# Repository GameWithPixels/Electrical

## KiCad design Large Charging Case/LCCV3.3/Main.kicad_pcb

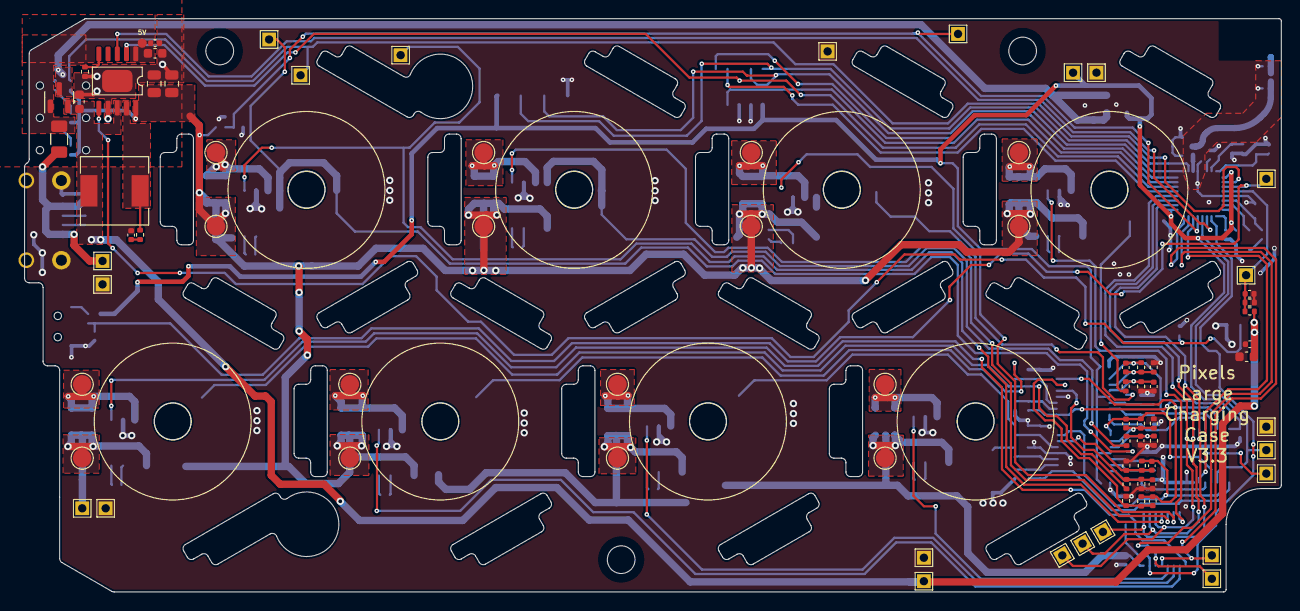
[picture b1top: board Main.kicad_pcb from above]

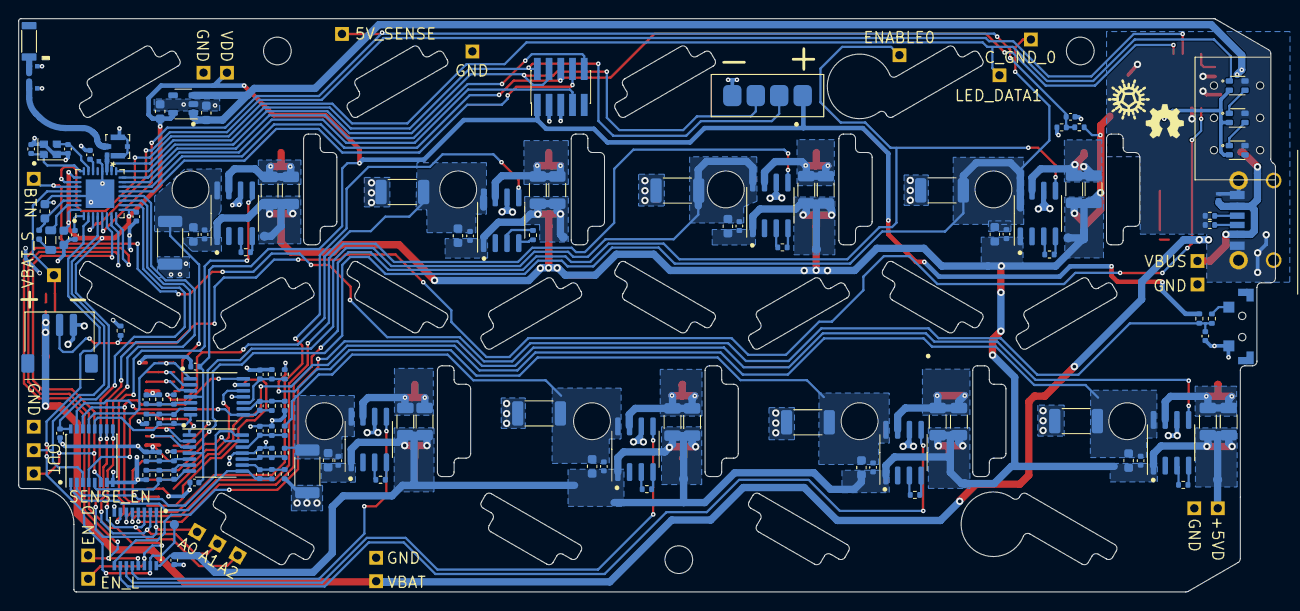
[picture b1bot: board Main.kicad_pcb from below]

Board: 2 copper layers, 136.2 x 62.1 mm, 225 parts (139 on the bottom side), 109 nets.

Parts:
AE1: Antenna_Chip; CHIP_ANT
C1, C2, C12, C16, C20, C24, C28, C32, C36, C44, C45, C52, C53, C56, C74: 10uF 10V 20%; C_0603_1608Metric
C3, C4, C10, C11, C15, C19, C23, C27, C31, C35, C39, C40, C41, C42, C43, C55, C75: 0.1uF 10V 20%; C_0402_1005Metric
C5, C6: 8pF 10V 10%; C_0402_1005Metric
C7: 100pF NP0 10V 5%; C_0402_1005Metric
C8, C9: 0.8pF 10V 5% NP0; 0402_RF
C13, C17, C21, C25, C29, C33, C37, C57: 100nF 50V NP0; C_1206_3216Metric
C14, C18, C22, C26, C30, C34, C38, C58: DNP; C_1206_3216Metric
C46: 3.3nF 50V 10%; C_0402_1005Metric
C47, C48: 22uF 10V 20%; C_0805_2012Metric
C49, C50, C59, C60, C61, C62, C63, C64, C65, C66, C67, C68, C69, C70, C71, C72: 1nF 10V 20%; C_0402_1005Metric
C51, C54: 10nF 25V 10%; C_0402_1005Metric
C73: DNP; 0402_RF
D1, D2, D3: TX1812Z_2020
D4: BAT54C; SOT-23
D5: D_TVS; DFN
F1: 1500mA <150mR; Fuse_1206_3216Metric
J1: Conn_02x05_Odd_Even; PinHeader_2x05_P1.27mm_Vertical_SMD
J2, J5, J8, J11, J14, J17, J20, J25: Coil B; TestPoint_Pad_D2.0mm
J3, J6, J9, J12, J15, J18, J21, J26: TX_Coil; TX Coil
J4, J7, J10, J13, J16, J19, J22, J27: Coil A; TestPoint_Pad_D2.0mm
J23: USB_C_Receptacle_USB2.0; USB-C-SMD_10P-P1.00-L6.8-W8.9
J24: Conn_01x03; Battery_Socket_1.5mm_3PIN
J28: DNP; MFH3.RECE.20369.001E.01
L1: 10uH 100mA 10%; L_0805_2012Metric
L2: 15nH; L_0402_1005Metric
L3: 1.5nH 5%; 0402_RF
L4: 2.2uH 1.5A 10%; SPM6530
L6: 3.9nH 5%; 0402_RF
P1: heard4; 4x2.54mm_SMD
R1: 10k 5%; R_0402_1005Metric
R2: 1k 1%; R_0402_1005Metric
R4, R7, R10, R13, R16, R33, R38, R74: 200K 1%; R_0402_1005Metric
R17: 82K 1%; R_0402_1005Metric
R18: 120k 1%; R_0402_1005Metric
R21, R25, R28, R32, R39, R43, R44, R48, R49, R53, R54, R58, R59, R63, R64, R68: 100k 0.1%; R_0402_1005Metric
R22, R24, R29, R31, R40, R42, R45, R47, R50, R52, R55, R57, R60, R62, R65, R67: 2k 0.1%; R_0402_1005Metric
R23, R30, R41, R46, R51, R56, R61, R66: 100mR 0.5W 1%; R_2010_5025Metric
R26, R27: 5.1k 1%; R_0402_1005Metric
R34, R71: 4.02M 1%; R_0402_1005Metric
R36, R72: 10M 1%; R_0402_1005Metric
R69: 1R 5%; R_0402_1005Metric
SW1: SW_Push; TSB002
U1: N52810_QFN32; QFN-32-1EP_5x5mm_P0.5mm_EP3.1x3.1mm
U3, U5, U7, U9, U11, U13, U15, U23: XKT520; SOIC-8_3.9x4.9mm_P1.27mm
U16: ETA9882; ESSOP10
U17: 74HC4051PW; SSOP-16_4.4x5.2mm_P0.65mm
U18, U20: LM2902; TSSOP-14_4.4x5mm_P0.65mm
U19: 74HCT259PW; SSOP-16_4.4x5.2mm_P0.65mm
U22: ME6215; SOT-23-5
W1: LED_DATA1; TestPoint_1.5x1.5_Drill0.9mm
W2, W3, W6, W7, W44, W45: GND; TestPoint_1.5x1.5_Drill0.9mm
W4, W9, W14, W19, W24, W29, W34, W71: R; TEST_PIN
W5: 5V_SENSE; TestPoint_1.5x1.5_Drill0.9mm
W11: VBAT; TestPoint_1.5x1.5_Drill0.9mm
W39: ENABLE0; TestPoint_1.5x1.5_Drill0.9mm
W40: C_GND_0; TestPoint_1.5x1.5_Drill0.9mm
W41: A2; TestPoint_1.5x1.5_Drill0.9mm
W42: A1; TestPoint_1.5x1.5_Drill0.9mm
W43: A0; TestPoint_1.5x1.5_Drill0.9mm
W47: OUT; TestPoint_1.5x1.5_Drill0.9mm
W48: SENSE_EN; TestPoint_1.5x1.5_Drill0.9mm
W57: EN_D; TestPoint_1.5x1.5_Drill0.9mm
W58: EN_L; TestPoint_1.5x1.5_Drill0.9mm
W59: CHARGER_CLR; TEST_PIN
W61: VBUS; TestPoint_1.5x1.5_Drill0.9mm
W62: 5V; TEST_PIN
W65: +5VD; TestPoint_1.5x1.5_Drill0.9mm
W68: VDD; TestPoint_1.5x1.5_Drill0.9mm
W70: VBAT_S; TestPoint_1.5x1.5_Drill0.9mm
W76: BTN; TestPoint_1.5x1.5_Drill0.9mm
Y1: 32MHz 40ppm; Crystal_SMD_2016-4Pin_2.0x1.6mm

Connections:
+5V: C43.1, C44.1, D4.1, F1.2, U16.1 (VIN), W62.1
+5VD: C11.1, C12.1, C13.2, C14.2, C15.1, C16.1, C17.2, C18.2, C19.1, C20.1, C21.2, C22.2, C23.1, C24.1, C25.2, C26.2, C27.1, C28.1, C29.2, C30.2, C31.1, C32.1, C33.2, C34.2, C35.1, C36.1, C37.2, C38.2, C42.1, C47.1, C48.1, C55.1, C56.1, C57.2, C58.2, D1.2 (VCC), D2.2 (VCC), D3.2 (VCC), J2.1, J5.1, J8.1, J11.1, J14.1, J17.1, J20.1, J25.1, R71.1, U3.1 (VDD), U5.1 (VDD), U7.1 (VDD), U9.1 (VDD), U11.1 (VDD), U13.1 (VDD), U15.1 (VDD), U16.10 (VOUT), U19.16 (VCC), U23.1 (VDD), W4.1, W9.1, W14.1, W19.1, W24.1, W29.1, W34.1, W65.1, W71.1
+BATT: C45.1, C74.1, C75.1, D4.2, J24.3, L4.2, R34.1, U16.8 (BAT), W11.1
/ANTENNA: AE1.1 (FEED), C73.1, L3.2
/ANT_50: C8.1, J28.4 (RF), L3.1, L6.2
/ANT_NRF: C9.1, L6.1, U1.19 (ANT)
/BOOST_EN: U1.3 (P0.01/XL2), U16.3 (ENBST)
/Multiplexed Chargers/CHARGER_ENL_D: U1.8 (P0.10), U19.13 (D), W57.1
/Multiplexed Chargers/CHARGER_SELECT_A0: U1.10 (P0.12), U17.11 (A), U19.1 (A0), W43.1
/Multiplexed Chargers/CHARGER_SELECT_A1: U1.11 (P0.14), U17.10 (B), U19.2 (A1), W42.1
/Multiplexed Chargers/CHARGER_SELECT_A2: U1.12 (P0.15), U17.9 (C), U19.3 (A2), W41.1
/Multiplexed Chargers/Charger 1/CHARGER_GND: C23.2, C24.2, R23.2, R24.1, U9.8 (PVSS), W40.1
/Multiplexed Chargers/Charger 1/XKT_OUT: C25.1, C26.1, J13.1, U9.7 (OUT)
/Multiplexed Chargers/Charger 2/CHARGER_GND: C11.2, C12.2, R30.2, R31.1, U3.8 (PVSS)
/Multiplexed Chargers/Charger 2/XKT_OUT: C13.1, C14.1, J4.1, U3.7 (OUT)
/Multiplexed Chargers/Charger 3/CHARGER_GND: C15.2, C16.2, R56.2, R57.1, U5.8 (PVSS)
/Multiplexed Chargers/Charger 3/XKT_OUT: C17.1, C18.1, J7.1, U5.7 (OUT)
/Multiplexed Chargers/Charger 4/CHARGER_GND: C19.2, C20.2, R51.2, R52.1, U7.8 (PVSS)
/Multiplexed Chargers/Charger 4/XKT_OUT: C21.1, C22.1, J10.1, U7.7 (OUT)
/Multiplexed Chargers/Charger 5/CHARGER_GND: C55.2, C56.2, R41.2, R42.1, U23.8 (PVSS)
/Multiplexed Chargers/Charger 5/XKT_OUT: C57.1, C58.1, J27.1, U23.7 (OUT)
/Multiplexed Chargers/Charger 6/CHARGER_GND: C27.2, C28.2, R46.2, R47.1, U11.8 (PVSS)
/Multiplexed Chargers/Charger 6/XKT_OUT: C29.1, C30.1, J16.1, U11.7 (OUT)
/Multiplexed Chargers/Charger 7/CHARGER_GND: C31.2, C32.2, R61.2, R62.1, U13.8 (PVSS)
/Multiplexed Chargers/Charger 7/XKT_OUT: C33.1, C34.1, J19.1, U13.7 (OUT)
/Multiplexed Chargers/Charger 8/CHARGER_GND: C35.2, C36.2, R66.2, R67.1, U15.8 (PVSS)
/Multiplexed Chargers/Charger 8/XKT_OUT: C37.1, C38.1, J22.1, U15.7 (OUT)
/Multiplexed Chargers/ENABLE0: U9.5 (FB), U19.4 (Q0), W39.1
/Multiplexed Chargers/ENABLE1: U3.5 (FB), U19.5 (Q1)
/Multiplexed Chargers/ENABLE2: U5.5 (FB), U19.6 (Q2)
/Multiplexed Chargers/ENABLE3: U7.5 (FB), U19.7 (Q3)
/Multiplexed Chargers/ENABLE4: U15.5 (FB), U19.9 (Q4)
/Multiplexed Chargers/ENABLE5: U13.5 (FB), U19.10 (Q5)
/Multiplexed Chargers/ENABLE6: U11.5 (FB), U19.11 (Q6)
/Multiplexed Chargers/ENABLE7: U19.12 (Q7), U23.5 (FB)
/Multiplexed Chargers/SENSE0: C49.2, R21.1, U17.5 (X5), U18.7
/Multiplexed Chargers/SENSE1: C59.2, R28.1, U17.4 (X7), U18.1
/Multiplexed Chargers/SENSE2: C67.2, R54.1, U17.12 (X3), U20.7
/Multiplexed Chargers/SENSE3: C65.2, R49.1, U17.13 (X0), U20.1
/Multiplexed Chargers/SENSE4: C61.2, R39.1, U17.1 (X4), U18.8
/Multiplexed Chargers/SENSE5: C63.2, R44.1, U17.2 (X6), U18.14
/Multiplexed Chargers/SENSE6: C69.2, R59.1, U17.15 (X2), U20.8
/Multiplexed Chargers/SENSE7: C71.2, R64.1, U17.14 (X1), U20.14
/Multiplexed Chargers/SENSE_OUT: U1.4 (P0.04/AIN2), U17.3 (X), W47.1
/Multiplexed Chargers/~CHARGER_CLR: U1.2 (P0.00/XL1), U19.15 (Clr), W59.1
/Multiplexed Chargers/~CHARGER_ENL_EN: U1.7 (P0.09), U19.14 (E), W58.1
/Multiplexed Chargers/~SENSE_EN: U1.6 (P0.06), U17.6 (ENABLE), W48.1
/Power/5V_SENSE: C51.1, R71.2, R72.1, U1.5 (P0.05/AIN3), W5.1
/VBAT_SENSE: C54.1, R34.2, R36.1, U1.28 (P0.30/AIN6), W70.1
GND: C1.2, C2.2, C3.2, C4.2, C5.1, C6.1, C7.2, C8.2, C9.2, C10.2, C39.2, C40.2, C41.2, C42.2, C43.2, C44.2, C45.2, C46.2, C47.2, C48.2, C50.2, C51.2, C52.2, C53.2, C54.2, C60.2, C62.2, C64.2, C66.2, C68.2, C70.2, C72.2, C73.2, C74.2, C75.2, D1.4 (GND), D2.4 (GND), D3.4 (GND), D5.1 (A1), J1.3, J1.5, J23.A12 (GND), J23.B12 (GND), J23.S1 (SHIELD), J24.1, J28.1, J28.2, J28.3, P1.4, R17.1, R18.2, R22.1, R23.1, R25.1, R26.1, R27.1, R29.1, R30.1, R32.1, R36.2, R40.1, R41.1, R43.1, R45.1, R46.1, R48.1, R50.1, R51.1, R53.1, R55.1, R56.1, R58.1, R60.1, R61.1, R63.1, R65.1, R66.1, R68.1, R72.2, SW1.2, U1.20 (VSS), U1.29 (VSS), U1.33 (VSS), U3.6 (VSS), U5.6 (VSS), U7.6 (VSS), U9.6 (VSS), U11.6 (VSS), U13.6 (VSS), U15.6 (VSS), U16.7 (VTERM), U16.11 (GND), U17.7 (V-), U17.8 (GND), U18.11 (V-), U19.8 (GND), U20.11 (V-), U22.2 (VSS), U23.6 (VSS), W2.1, W3.1, W6.1, W7.1, W44.1, W45.1, Y1.2, Y1.4
unnamed: C1.1, L2.2, U1.30 (DEC4)
unnamed: C3.1, R1.1, R2.2, U1.27 (P0.28/AIN4), W76.1
unnamed: C4.1, U1.1 (DEC1)
unnamed: C5.2, U1.24 (XC2), Y1.1
unnamed: C6.2, U1.23 (XC1), Y1.3
unnamed: C7.1, U1.22 (DEC3)
unnamed: C46.1, R69.1
unnamed: C49.1, R21.2, R22.2, U18.6 (-)
unnamed: C50.1, R24.2, R25.2, U18.5 (+)
unnamed: C53.1, D4.3, U22.1 (VIN), U22.3 (CE)
unnamed: C59.1, R28.2, R29.2, U18.2 (-)
unnamed: C60.1, R31.2, R32.2, U18.3 (+)
unnamed: C61.1, R39.2, R40.2, U18.9 (-)
unnamed: C62.1, R42.2, R43.2, U18.10 (+)
unnamed: C63.1, R44.2, R45.2, U18.13 (-)
unnamed: C64.1, R47.2, R48.2, U18.12 (+)
unnamed: C65.1, R49.2, R50.2, U20.2 (-)
unnamed: C66.1, R52.2, R53.2, U20.3 (+)
unnamed: C67.1, R54.2, R55.2, U20.6 (-)
unnamed: C68.1, R57.2, R58.2, U20.5 (+)
unnamed: C69.1, R59.2, R60.2, U20.9 (-)
unnamed: C70.1, R62.2, R63.2, U20.10 (+)
unnamed: C71.1, R64.2, R65.2, U20.13 (-)
unnamed: C72.1, R67.2, R68.2, U20.12 (+)
unnamed: D1.1 (DIN), D2.3 (DOUT)
unnamed: D2.1 (DIN), D3.3 (DOUT)
unnamed: D3.1 (DIN), U1.26 (P0.25), W1.1
unnamed: J23.A5 (CC1), R27.2
unnamed: J23.B5 (CC2), R26.2
unnamed: J24.2, R17.2, U16.6 (NTC)
unnamed: L1.1, U1.31 (DCC)
unnamed: L1.2, L2.1
unnamed: L4.1, R69.2, U16.9 (SW)
unnamed: R2.1, SW1.1
unnamed: R4.1, U3.4 (R)
unnamed: R4.2, U3.3 (R)
unnamed: R7.1, U5.4 (R)
unnamed: R7.2, U5.3 (R)
unnamed: R10.1, U7.4 (R)
unnamed: R10.2, U7.3 (R)
unnamed: R13.1, U9.4 (R)
unnamed: R13.2, U9.3 (R)
unnamed: R16.1, U11.4 (R)
unnamed: R16.2, U11.3 (R)
unnamed: R18.1, U16.5 (ISET)
unnamed: R33.1, U13.4 (R)
unnamed: R33.2, U13.3 (R)
unnamed: R38.1, U15.4 (R)
unnamed: R38.2, U15.3 (R)
unnamed: R74.1, U23.4 (R)
unnamed: R74.2, U23.3 (R)
RESET: J1.10, U1.16 (P0.16)
RXI: J1.7, U1.15 (P0.20/TCLK)
SWDCLK: J1.4, P1.3, U1.17 (SWDCLK)
SWDIO: J1.2, P1.2, U1.18 (SWDIO)
SWO: J1.6, U1.14 (P0.18/TDATA0), U16.2 (STAT)
TXO: J1.8, U1.13 (P0.16/TDATA1)
VBUS: D5.2 (A2), F1.1, J23.A9 (VBUS), J23.B9 (VBUS), W61.1
VDD: C2.1, C10.1, C39.1, C40.1, C41.1, C52.1, J1.1, P1.1, R1.2, U1.9 (VDD), U1.25 (VDD), U1.32 (VDD), U17.16 (V+), U18.4 (V+), U20.4 (V+), U22.5 (VOUT), W68.1

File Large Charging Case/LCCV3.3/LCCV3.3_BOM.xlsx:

Item | Qty | Reference(s) | Value | Manufacturer Part Number | LCSC Part Number | Footprint | Manufacturer
1 | 1 | AE1 | Antenna_Chip | MGMA3216H2450-A02 | C486319 | Pixels-dice:CHIP_ANT | Microgate
2 | 15 | C1, C2, C12, C16, C20, C24, C28, C32, C36, C44, C45, C52, C53, C56, C74 | 10uF 10V 20% X5R | GRM188R61A106ME69D | C90053 | Capacitor_SMD:C_0603_1608Metric | Murata
3 | 17 | C3, C4, C10, C11, C15, C19, C23, C27, C31, C35, C39, C40, C41, C42, C43, C55, C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 | 0.1uF 16V 10% X7R | GRM155R71C104KA88D | C71629 | Capacitor_SMD:C_0402_1005Metric | Murata
4 | 2 | C5, C6 | 8pF 10V 10% | GRT1555C2A8R0DA02D |  | Capacitor_SMD:C_0402_1005Metric | Murata
5 | 1 | C7 | 100pF 50V NP0 | GCM1555C1H101JA16J | C3888756 | Capacitor_SMD:C_0402_1005Metric | Murata
6 | 2 | C8, C9 | 0.8pF 50V 5% NP0 | GJM1555C1HR80BB01D | C76915 | Pixels-dice:0402_RF | Murata
7 | 8 | C13, C17, C21, C25, C29, C33, C37, C57 | 100nF 50V NP0 | GRM31C5C1H104JA01L | C97946 | Capacitor_SMD:C_1206_3216Metric | Murata
8 | 8 | C14, C18, C22, C26, C30, C34, C38, C58 | DNP |  |  | Capacitor_SMD:C_1206_3216Metric
9 | 1 | C46 | 3.3nF 50V 10% X7R | GRM155R71H332KA01D | C85963 | Capacitor_SMD:C_0402_1005Metric | Murata
10 | 2 | C47, C48 | 22uF 25V 20% X5R | GRM21BR61E226ME44L | C86816 | Capacitor_SMD:C_0805_2012Metric | Murata
11 | 16 | C49, C50, C59, C60, C61, C62, C63, C64, C65, C66, C67, C68, C69, C70, C71, C72 | 1nF 50V 10% X7R | GRM155R71H102KA01D | C77018 | Capacitor_SMD:C_0402_1005Metric | Murata
12 | 2 | C51, C54 | 10nF 50V 10% X7R | GRM155R71H103KA88D | C77019 | Capacitor_SMD:C_0402_1005Metric | Murata
13 | 1 | C73 | DNP |  |  | Pixels-dice:0402_RF
14 | 3 | D1, D2, D3 | TX1812Z_2020 | TC2020RGB-3CJH-TX1812Z5 | C784564 | Pixels-dice:TX1812Z_2020 | TCWIN
15 | 1 | D4 | BAT54C | BAT54C,215 | C37704 | Package_TO_SOT_SMD:SOT-23 | Nexperia
16 | 1 | D5 | D_TVS | LXES1UTAA1-157 |  | Pixels-dice:DFN | Murata
17 | 1 | F1 | 1500mA <150mR | ASMD1206-150 | C135341 | Fuse:Fuse_1206_3216Metric | Shenzhen JDT Fuse
18 | 1 | J1 | Conn_02x05_Odd_Even | X1270WVS-2x05B-6TV01 | C2962219 | Connector_PinHeader_1.27mm:PinHeader_2x05_P1.27mm_Vertical_SMD | XKB Connectivity
19 | 1 | J23 | USB_C_Receptacle_USB2.0 | TYPE-C-31-M-17 | C283540 | Pixels-dice:USB-C-SMD_10P-P1.00-L6.8-W8.9 | Korean Hroparts Elec
20 | 1 | J24 | Conn_01x03 | S3B-ZR-SM4A-TF | C72591 | Pixels-dice:Battery_Socket_1.5mm_3PIN | ZH CONNECTOR
21 | 1 | J28 | DNP |  |  | RFFrontEnd:MFH3.RECE.20369.001E.01
22 | 1 | L1 | 10uH 100mA 20% | LQM21FN100M80L | C162582 | Inductor_SMD:L_0805_2012Metric | Murata
23 | 1 | L2 | 15nH 320mR 5% | LQG15HS15NJ02D | C86059 | Inductor_SMD:L_0402_1005Metric | Murata
24 | 1 | L3 | 1.5nH 5% | LQG15WZ1N5B02D | C3910911 | Pixels-dice:0402_RF | Murata
25 | 1 | L4 | 2.2uH 1.5A 10% | SPM6530T-2R2M | C76857 | Pixels-dice:SPM6530 | TDK
26 | 1 | L6 | 3.9nH 5% | LQG15HS3N9B02D |  | Pixels-dice:0402_RF | Murata
27 | 1 | R1 | 10k 1% | 0402WGF1002TCE | C25744 | Resistor_SMD:R_0402_1005Metric | UNI-ROYAL(Uniroyal Elec)
28 | 1 | R2 | 1k 1% | 0402WGF1001TCE | C11702 | Resistor_SMD:R_0402_1005Metric | UNI-ROYAL(Uniroyal Elec)
29 | 8 | R4, R7, R10, R13, R16, R33, R38, R74 | 200K 1% | 0402WGF2003TCE | C25764 | Resistor_SMD:R_0402_1005Metric | UNI-ROYAL(Uniroyal Elec)
30 | 1 | R17 | 82K 1% | 0402WGF8202TCE | C4142 | Resistor_SMD:R_0402_1005Metric | UNI-ROYAL(Uniroyal Elec)
31 | 1 | R18 | 120K 1% | 0402WGF1203TCE | C25750 | Resistor_SMD:R_0402_1005Metric | UNI-ROYAL(Uniroyal Elec)
32 | 16 | R21, R25, R28, R32, R39, R43, R44, R48, R49, R53, R54, R58, R59, R63, R64, R68 | 100K 0.1% | RT0402BRD07100KL | C852472 | Resistor_SMD:R_0402_1005Metric | YAGEO
33 | 16 | R22, R24, R29, R31, R40, R42, R45, R47, R50, R52, R55, R57, R60, R62, R65, R67 | 2K 0.1% | RT0402BRD072KL | C852711 | Resistor_SMD:R_0402_1005Metric | YAGEO
34 | 8 | R23, R30, R41, R46, R51, R56, R61, R66 | 100mR 0.75W 1% | RL2010FK-070R1L | C309644 | Resistor_SMD:R_2010_5025Metric | YAGEO
35 | 2 | R26, R27 | 5.1k 1% | 0402WGF5101TCE | C25905 | Resistor_SMD:R_0402_1005Metric | UNI-ROYAL(Uniroyal Elec)
36 | 2 | R34, R71 | 4.02M 1% | 0402WGF4024TCE | C423177 | Resistor_SMD:R_0402_1005Metric | UNI-ROYAL(Uniroyal Elec)
37 | 2 | R36, R72 | 10M 1% | 0402WGF1005TCE | C26082 | Resistor_SMD:R_0402_1005Metric | UNI-ROYAL(Uniroyal Elec)
38 | 1 | R69 | 1R 5% | 0402WGJ010JTCE | C25147 | Resistor_SMD:R_0402_1005Metric | UNI-ROYAL(Uniroyal Elec)
39 | 1 | SW1 | SW_Push | TSB001A3526A02 | C2888889 | Pixels-dice:TSB002 | BZCN
40 | 1 | U1 | N52810_QFN32 | NRF52810-QCAA-R |  | Package_DFN_QFN:QFN-32-1EP_5x5mm_P0.5mm_EP3.1x3.1mm | Nordic Semiconductor
41 | 8 | U3, U5, U7, U9, U11, U13, U15, U23 | XKT520 |  |  | Pixels-dice:SOIC-8_3.9x4.9mm_P1.27mm
42 | 1 | U16 | ETA9882 | ETA9882E10 |  | Pixels-dice:ESSOP10 | ETA Semiconductor Limited
43 | 1 | U17 | 74HC4051PW | 74HC4051PW,118 | C5645 | Package_SO:SSOP-16_4.4x5.2mm_P0.65mm | Nexperia
44 | 2 | U18, U20 | LM2902 | LM2902PWR | C46864 | Package_SO:TSSOP-14_4.4x5mm_P0.65mm | Texas Instrument
45 | 1 | U19 | 74HCT259PW | 74HCT259PW,118 | C478149 | Package_SO:SSOP-16_4.4x5.2mm_P0.65mm | Nexperia
46 | 1 | U22 | ME6215 | ME6215C30M5G | C236664 | Pixels-dice:SOT-23-5 | MICRONE(Nanjing Micro One Elec)
47 | 1 | Y1 | 32MHz 40ppm | XRCGB32M000F2P00R0 | C527602 | Pixels-dice:Crystal_SMD_2016-4Pin_2.0x1.6mm | Murata
